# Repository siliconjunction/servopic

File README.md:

# A PIC based distributed servo controller

## Overview
This project build a PIC based controller for a servo motor. The controllers can be daisy chained so that the host just needs a single serial port to drive multiple servo motors. A series of blogs on the <a href="http://siliconjunction.blogspot.com.au">Silicon Junction blog</a> starting with <a href="http://siliconjunction.blogspot.com/2020/03/daisy-chain-servo-controller.html">this one</a> provides more information.

<br/>
<center></center>
<br/>

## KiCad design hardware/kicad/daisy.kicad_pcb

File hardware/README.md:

# KiCAD PCB files

## Overview

<br/>
<center></center>
<br/>
<center></center>
<br/>

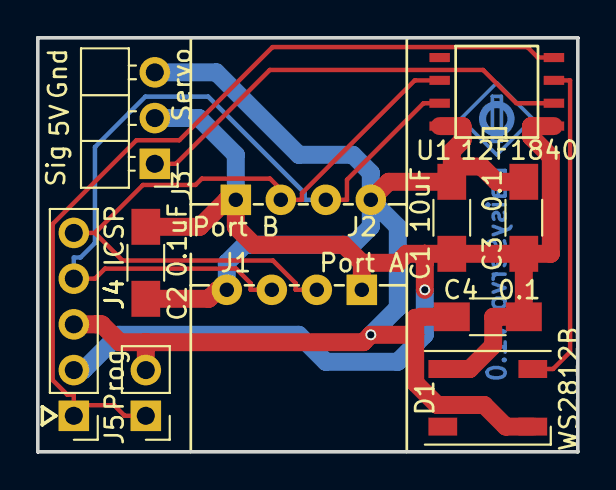
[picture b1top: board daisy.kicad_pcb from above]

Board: 2 copper layers, 30.0 x 23.0 mm, 11 parts (0 on the bottom side), 7 nets.

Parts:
C1: 10uF; C_1206_HandSoldering
C2: 0.1uF; C_1206_HandSoldering
C3, C4: 0.1; C_1206_HandSoldering
D1: WS2812B; LED_WS2812B-PLCC4
J1: Port A; XH2.5_Angled_1x04
J2: Port B; XH2.5_Angled_1x04
J3: Servo; Pin_Header_Angled_1x03_Pitch2.54mm
J4: ICSP; Pin_Header_Straight_1x05_Pitch2.54mm
J5: Prog; Pin_Header_Straight_1x02_Pitch2.54mm
U1: 12F1840; SOIC-8-N

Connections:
+5V: C1.1, C2.1, C3.1, C4.1, D1.1, J1.1, J2.1, J3.2, J4.2, U1.1
GND: C1.2, C2.2, C3.2, C4.2, D1.3, J1.4, J2.4, J3.3, J4.3, J5.2, U1.8
unnamed: D1.4, U1.3
unnamed: J1.2, J2.2, J4.5, U1.6
unnamed: J1.3, J2.3, J4.4, U1.7
unnamed: J3.1, U1.2
unnamed: J4.1, J5.1, U1.4

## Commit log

2020-03-07 Added readme
2020-03-07 Added kicad files
2020-03-07 Added PIC firmware
2020-03-08 Expanded description a little
2020-03-08 Update diagram
